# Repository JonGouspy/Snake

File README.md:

# Snake – PCB

## Informations générales

* **Nom du projet** : Snake
* **Version** : v1.0
* **Date** : 30/04/2026
* **Groupe** : 1
* **Membres du groupe** : jon.gouspy, alexandre.lacroix, valentin.delhommeau

---

## Fichiers fournis

* **Gerber files ** : fabrication des couches PCB (./kicad/gerbers)
* **Drill files (.drl)** : perçage (./kicad/gerbers)
* **BOM** : liste des composants (./kicad)

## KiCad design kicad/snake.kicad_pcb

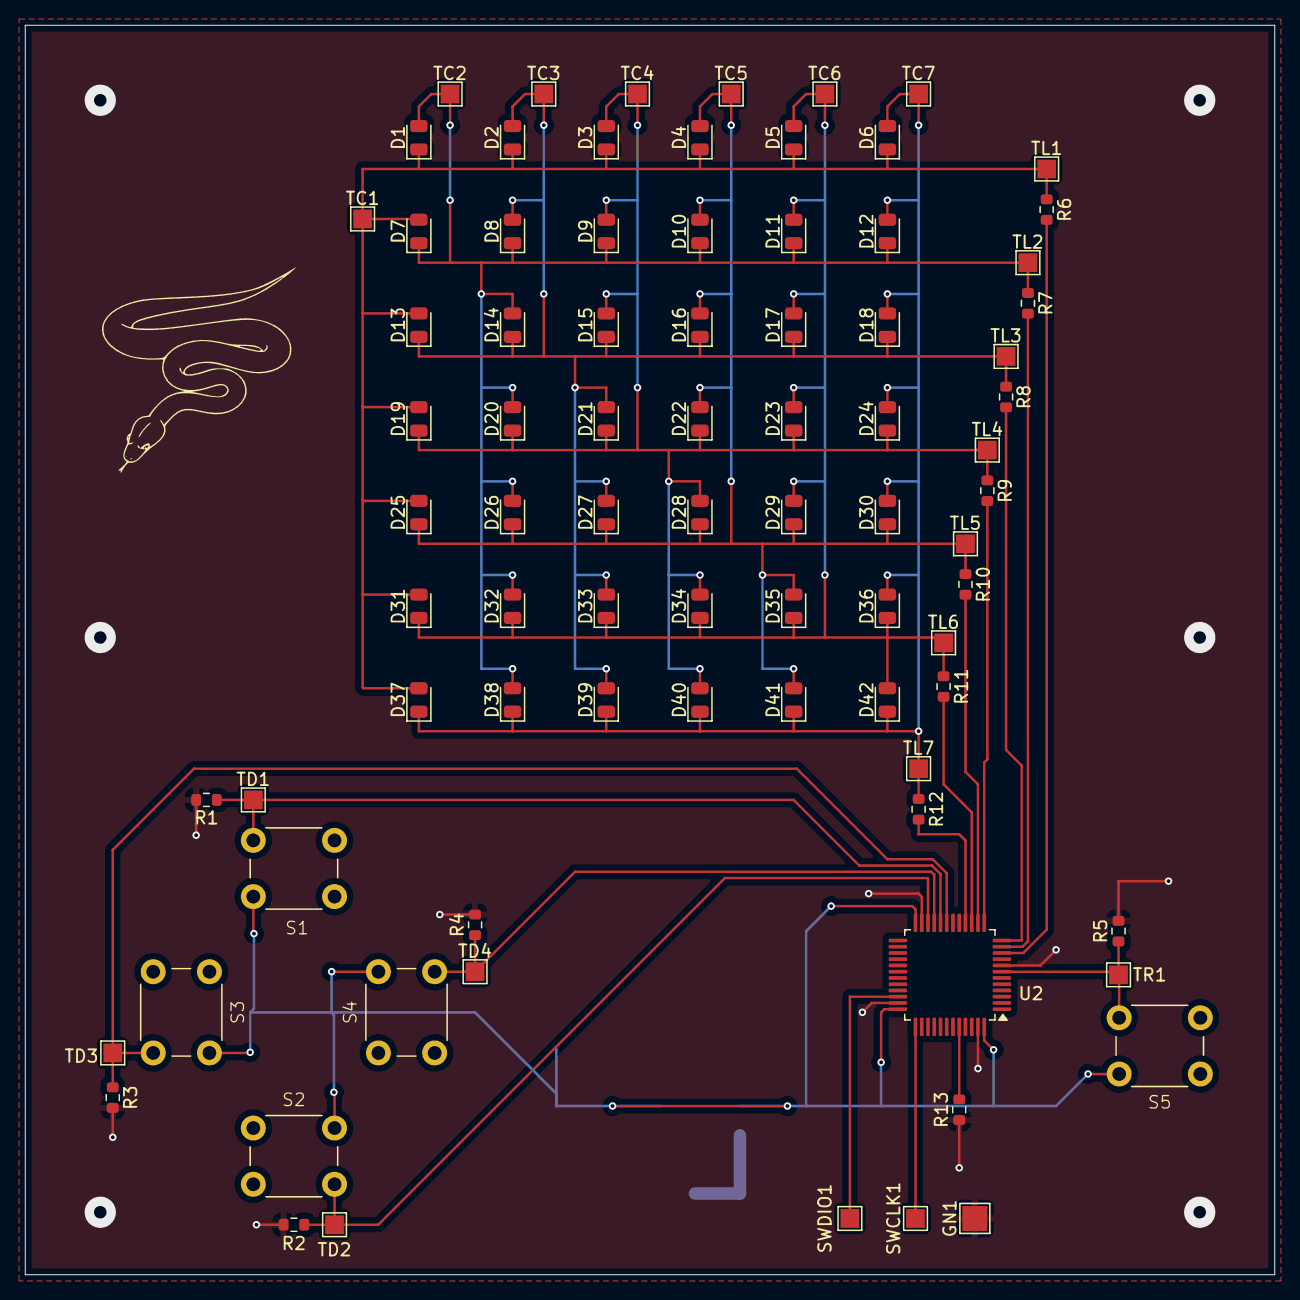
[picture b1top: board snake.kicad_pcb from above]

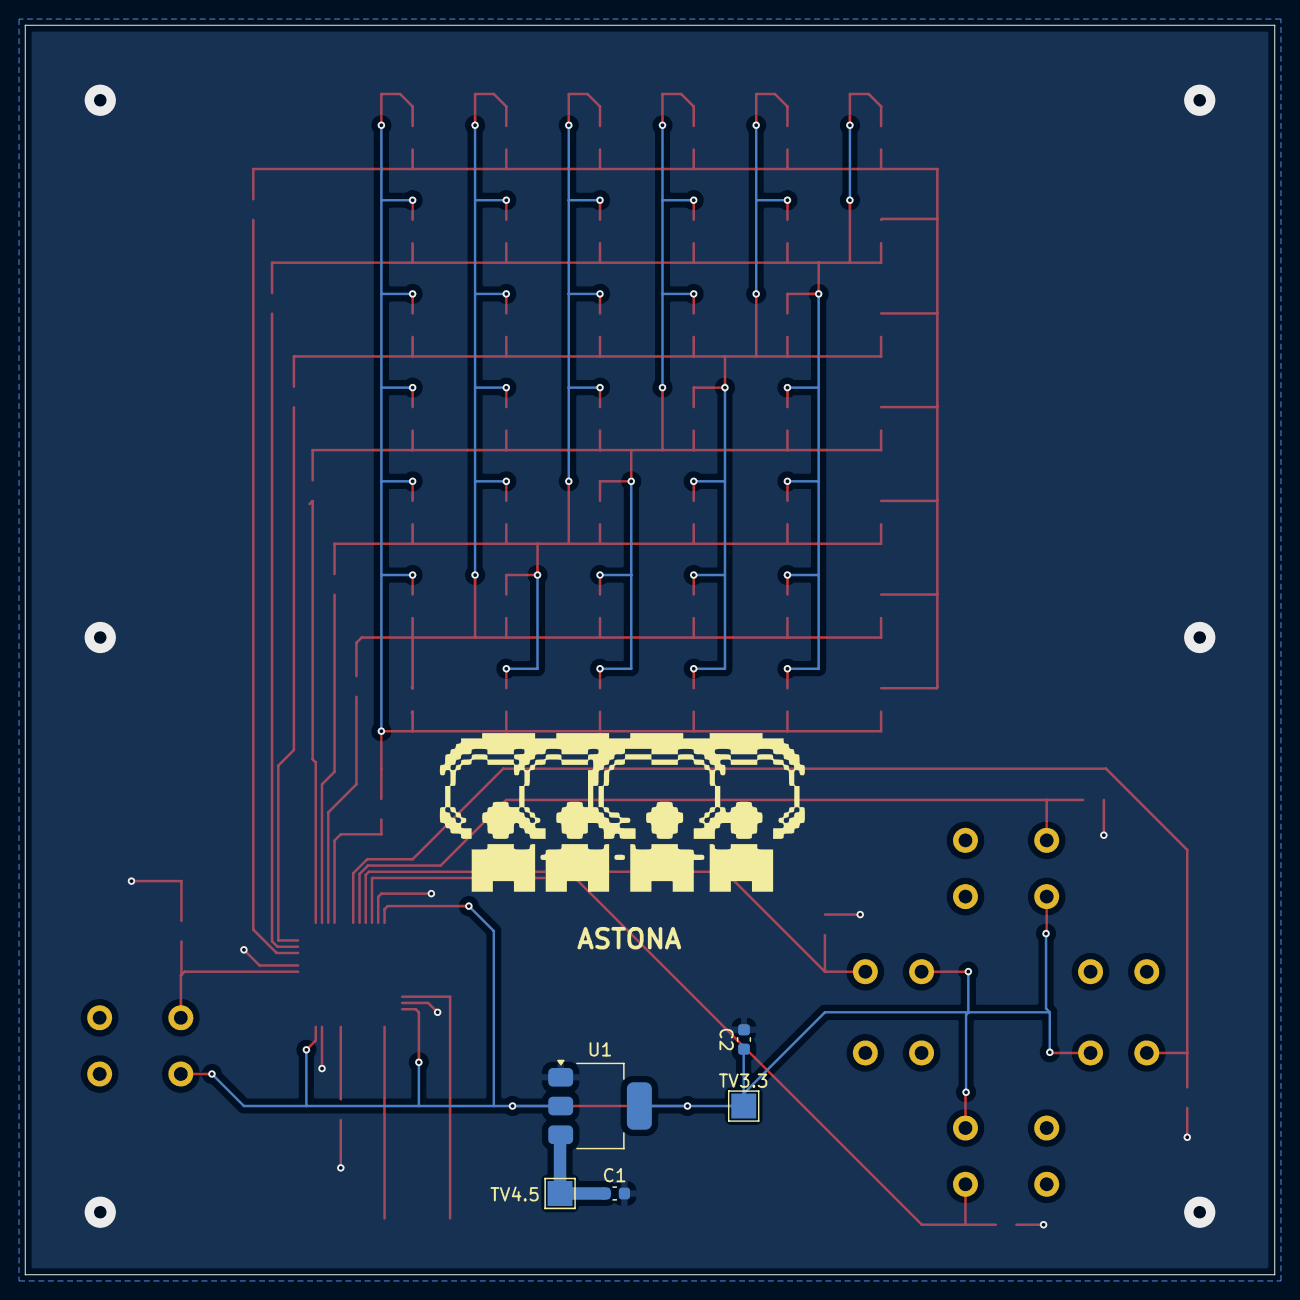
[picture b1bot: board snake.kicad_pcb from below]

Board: 2 copper layers, 100.0 x 100.0 mm, 90 parts (6 on the bottom side), 25 nets.

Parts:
ASTONA: LOGO
C1, C2: 1uF; C_0603_1608Metric
D1, D2, D3, D4, D5, D6, D7, D8, D9, D10, D11, D12, D13, D14, D15, D16, D17, D18, D19, D20, D21, D22, D23, D24, D25, D26, D27, D28, D29, D30, D31, D32, D33, D34, D35, D36, D37, D38, D39, D40, D41, D42: WL-SMCW_0805; LED_0805_2012Metric
GN1: TestPoint_Small; TestPoint_Pad_2.0x2.0mm
R1, R2, R3, R4, R5, R13: 10K; R_0603_1608Metric
R6, R7, R8, R9, R10, R11, R12: 220; R_0603_1608Metric
S1, S2, S3, S4, S5: B3F-1000; SW_Push_6mm_4P
SWCLK1: TestPoint_Small; TestPoint_Pad_1.5x1.5mm
SWDIO1: TestPoint_Small; TestPoint_Pad_1.5x1.5mm
Snake: LOGO
TC1, TC2, TC3, TC4, TC5, TC6, TC7: TestPoint_Small; TestPoint_Pad_1.5x1.5mm
TD1, TD2, TD3, TD4: TestPoint_Small; TestPoint_Pad_1.5x1.5mm
TL1, TL2, TL3, TL4, TL5, TL6, TL7: TestPoint_Small; TestPoint_Pad_1.5x1.5mm
TR1: TestPoint_Small; TestPoint_Pad_1.5x1.5mm
TV3.3, TV4.5: TestPoint_Small; TestPoint_Pad_2.0x2.0mm
U1: LD1117S33TR_SOT223; SOT-223-3_TabPin2
U2: STM32F103C8Tx; LQFP-48_7x7mm_P0.5mm

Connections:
+3.3V: C2.1, S1.1, S2.1, S3.1, S4.1, S5.1, TV3.3.1, U1.2 (VO), U2.24 (VDD), U2.36 (VDD), U2.48 (VDD)
+4.5V: C1.1, TV4.5.1, U1.3 (VI)
/Down: R2.1, S2.2, TD2.1, U2.22 (PB11)
/L1: R6.2, U2.10 (PA0)
/L2: R7.2, U2.11 (PA1)
/L3: R8.2, U2.12 (PA2)
/L4: R9.2, U2.13 (PA3)
/L5: R10.2, U2.14 (PA4)
/L6: R11.2, U2.15 (PA5)
/L7: R12.2, U2.16 (PA6)
/Left: R3.1, S3.2, TD3.1, U2.19 (PB1)
/RST: R5.1, S5.2, TR1.1, U2.7 (NRST)
/Right: R4.1, S4.2, TD4.1, U2.21 (PB10)
/SWCLK: SWCLK1.1, U2.37 (PA14)
/SWDIO: SWDIO1.1, U2.34 (PA13)
/Up: R1.1, S1.2, TD1.1, U2.20 (PB2)
GND: C1.2, C2.2, GN1.1, R1.2, R2.2, R3.2, R4.2, R5.2, R13.1, U1.1 (GND), U2.8 (VSSA), U2.23 (VSS), U2.35 (VSS), U2.47 (VSS)
unnamed: D1.1, D2.1, D3.1, D4.1, D5.1, D6.1, D7.2, D13.2, D19.2, D25.2, D31.2, D37.2, R6.1, TC1.1, TL1.1
unnamed: D1.2, D7.1, D8.1, D9.1, D10.1, D11.1, D12.1, D14.2, D20.2, D26.2, D32.2, D38.2, R7.1, TC2.1, TL2.1
unnamed: D4.2, D10.2, D16.2, D22.2, D25.1, D26.1, D27.1, D28.1, D29.1, D30.1, D35.2, D41.2, R10.1, TC5.1, TL5.1
unnamed: D5.2, D11.2, D17.2, D23.2, D29.2, D31.1, D32.1, D33.1, D34.1, D35.1, D36.1, D42.2, R11.1, TC6.1, TL6.1
unnamed: D6.2, D12.2, D18.2, D24.2, D30.2, D36.2, D37.1, D38.1, D39.1, D40.1, D41.1, D42.1, R12.1, TC7.1, TL7.1
unnamed: D2.2, D8.2, D13.1, D14.1, D15.1, D16.1, D17.1, D18.1, D21.2, D27.2, D33.2, D39.2, R8.1, TC3.1, TL3.1
unnamed: D3.2, D9.2, D15.2, D19.1, D20.1, D21.1, D22.1, D23.1, D24.1, D28.2, D34.2, D40.2, R9.1, TC4.1, TL4.1
unnamed: R13.2, U2.44 (BOOT0)

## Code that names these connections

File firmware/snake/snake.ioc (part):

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Mcu.Name=STM32F103C(8-B)Tx
Mcu.Package=LQFP48
Mcu.UserName=STM32F103C8Tx
PA0-WKUP.Signal=GPIO_Output
PA1.Signal=GPIO_Output
PA13.Mode=Serial_Wire
PA13.Signal=SYS_JTMS-SWDIO
PA14.Mode=Serial_Wire
PA14.Signal=SYS_JTCK-SWCLK
PA2.Signal=GPIO_Output
PA3.Signal=GPIO_Output
PA4.Signal=GPIO_Output
PA5.Signal=GPIO_Output
PA6.Signal=GPIO_Output
PB1.Signal=GPIO_Input
PB10.Signal=GPIO_Input
PB11.Signal=GPIO_Input
PB2.Signal=GPIO_Input
board=custom

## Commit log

2026-03-28 feat: gitignore + first charlieplexing
2026-03-28 feat: led components
2026-04-02 feat: other schematics
2026-04-08 feat: led resistances
2026-04-08 feat: stm32 add must plug the houssing
2026-04-09 feat: new components + cleaner
2026-04-09 feat: link, must add ST-Link
2026-04-09 chore: cleaner
2026-04-09 feat: interface must add component
2026-04-09 chore: delete useless files
2026-04-28 fix: no more error & warning
2026-04-28 fix: ground below and vcc above
2026-04-28 feat: test point
2026-04-28 chore: title
2026-04-29 feat: footprint must patch button
2026-04-29 fix: switch button footprint
2026-04-29 feat(pcb): first PCB placement
2026-04-29 fix(pcb): moving mcu + regul
2026-04-29 feat: first connection led
2026-04-30 feat: charlieplexing
2026-04-30 feat: more connection
2026-04-30 feat: wire
2026-04-30 feat: plan de masse
2026-04-30 feat: BOM
2026-04-30 feat: image
2026-04-30 feat: rm none used schematics
2026-04-30 feat: better library
2026-04-30 feat(result): generate BOM, GERBERS, NC
2026-04-30 fix(readme): typos README.md
2026-06-16 feat: led test firmware
